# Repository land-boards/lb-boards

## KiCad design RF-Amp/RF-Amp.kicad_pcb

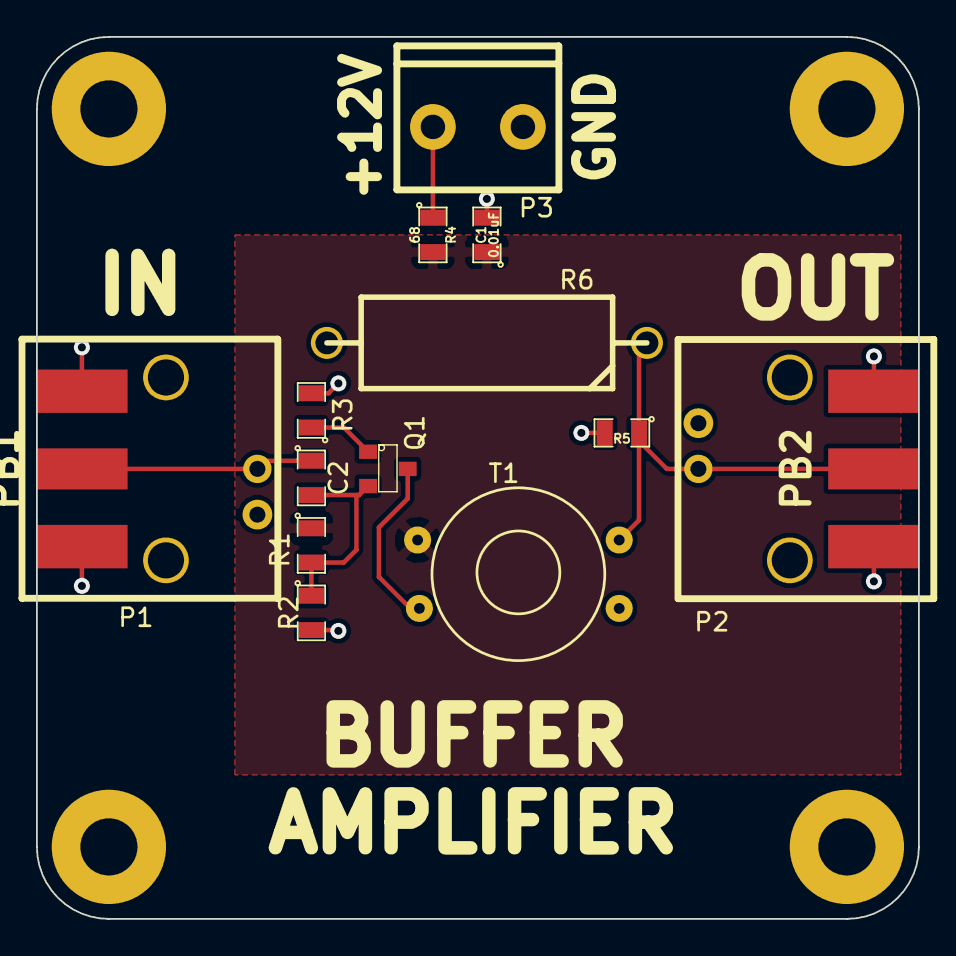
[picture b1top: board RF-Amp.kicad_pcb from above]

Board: 2 copper layers, 49.0 x 49.0 mm, 19 parts (0 on the bottom side), 8 nets.

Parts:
C1: 0.01uF; SM0805
C2: C; SM0805
MTG1, MTG2, MTG3, MTG4: CONN_1; MTG-4-40
P1, P2: BNC; BNC-RT
P3: CONN_2; TB2-5MM
PB1, PB2: CONN_2; SMA_EDGE
Q1: 2N3904; SOT23
R1: 22K; SM0805
R2: R; SM0805
R3: 180; SM0805
R4: 68; SM0805
R5: DNP; SM0805
R6: DNP; R7
T1: TRANSFO; TRANS-37-43

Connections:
/+12V: P3.1, R4.1
/+BUF: C1.1, R1.1, R4.2, T1.1
/GND: C1.2, P1.2, P2.2, P3.2, PB1.2, PB2.2, R2.2, R3.2, R5.2, R6.2, T1.3
/IN: C2.1, P1.1, PB1.1
/OUT: P2.1, PB2.1, R5.1, R6.1, T1.4
/VB: C2.2, Q1.2, R1.2, R2.1
/VC: Q1.3, T1.2
unnamed: Q1.1, R3.1

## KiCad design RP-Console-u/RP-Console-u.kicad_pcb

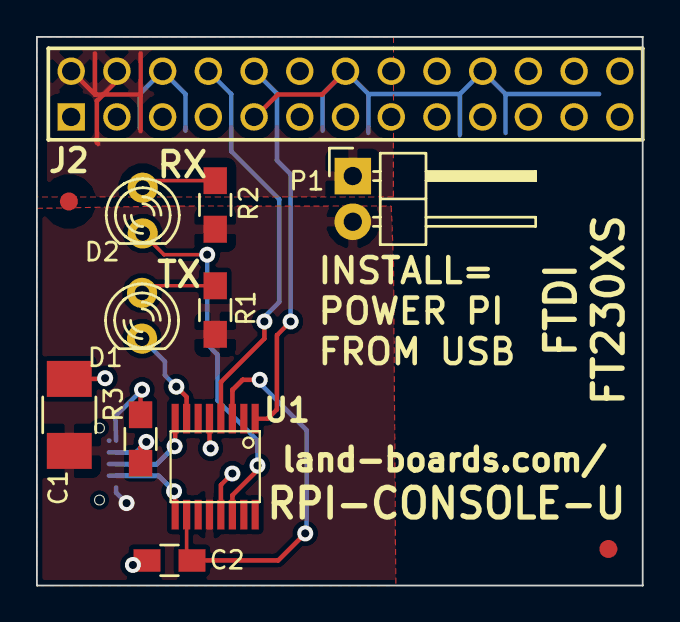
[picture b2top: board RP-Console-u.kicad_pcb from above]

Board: 2 copper layers, 33.7 x 30.5 mm, 13 parts (1 on the bottom side), 13 nets.

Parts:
C1: 10uF; C_1210_HandSoldering
C2: 0.1uF; C_0805_HandSoldering
D1, D2: LED; LED-3MM
FID1, FID2: CONN_1; FIDUCIAL
J1: USB-MICRO-B; USB_Micro-B-Wellco-SMT
J2: RASPIO; pin_array_13x2
P1: CONN_2; Pin_Header_Angled_1x02
R1, R2: 270; R_0805_HandSoldering
R3: 130K; R_0805_HandSoldering
U1: FT230XS; ssop-16

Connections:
/+3.3V-USB: C2.1, U1.3, U1.10
/+5V: J2.2, J2.4, P1.1
/+5V-USB: C1.1, J1.1, P1.2, R1.1, R2.1, U1.12
/DM: J1.2, U1.9
/DP: J1.3, U1.8
/GND: C1.2, C2.2, J1.5, J2.6, J2.9, J2.14, J2.20, J2.25, R3.2, U1.5, U1.13
/PI2USB: J2.8, U1.4
/PUP0: D1.1, R1.2
/PUP1: D2.1, R2.2
/RXLED*: D2.2, U1.14
/TXLED*: D1.2, U1.7
/USB2PI: J2.10, U1.1
unnamed: J1.4, R3.1

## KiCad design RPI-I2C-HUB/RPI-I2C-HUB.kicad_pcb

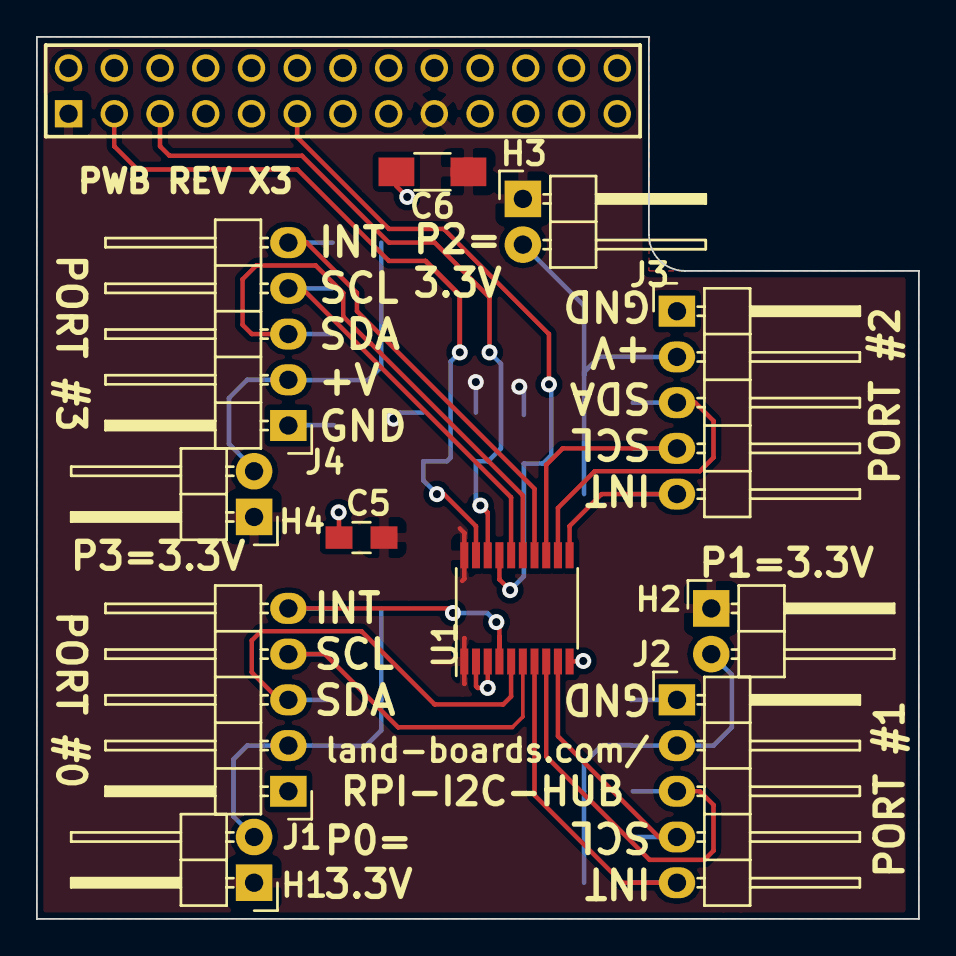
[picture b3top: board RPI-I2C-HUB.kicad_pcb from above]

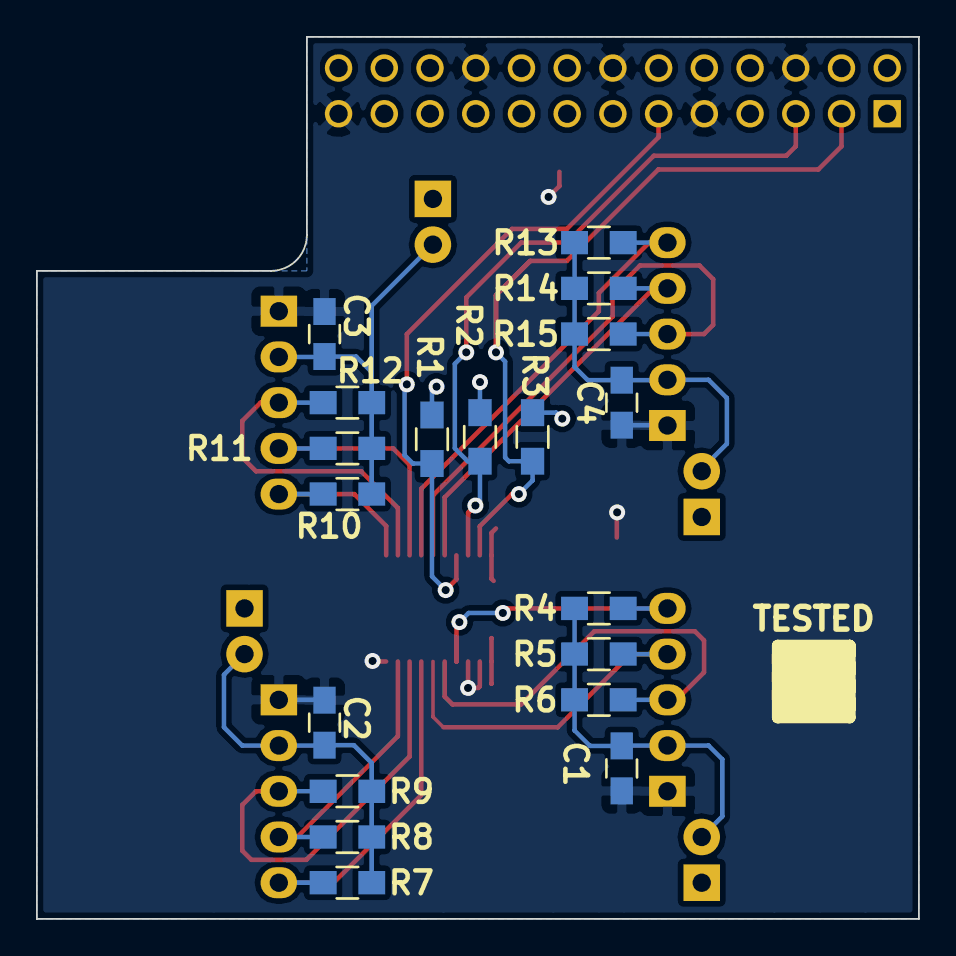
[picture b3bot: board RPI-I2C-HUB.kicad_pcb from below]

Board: 2 copper layers, 49.0 x 49.0 mm, 32 parts (19 on the bottom side), 21 nets.

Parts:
C1, C2, C3, C4, C5: 0.1uF; C_0805_HandSoldering
C6: 10uF; C_1206_HandSoldering
H1, H2, H3, H4: CONN_01X02; Pin_Header_Angled_1x02
J1, J2, J3, J4: I2CINT-5PIN; Pin_Header_Angled_1x05
P1: RASPIO; pin_array_13x2
R1, R2, R3, R4, R5, R6, R7, R8, R9, R10, R11, R12, R13, R14, R15: 3.3K; R_0805_HandSoldering
TESTED: VAL**; TEST_BLK-REAR
U1: PCA9544A; TSSOP-20_4.4x6.5mm_Pitch0.65mm

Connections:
+3.3V: C5.1, C6.1, H1.1, H2.1, H3.1, H4.1, P1.1, P1.17, R1.1, R2.1, R3.1, U1.1, U1.20
/IO_17: P1.11, R1.2, U1.17
/SCLK1: P1.5, R2.2, U1.18
/SDA1: P1.3, R3.2, U1.19
/~I0: J1.5, R4.2, U1.4
/~I1: J2.5, R7.2, U1.7
/~I2: J3.5, R10.2, U1.11
/~I3: J4.5, R13.2, U1.14
GND: C1.2, C2.2, C3.2, C4.2, C5.2, C6.2, J1.1, J2.1, J3.1, J4.1, P1.6, P1.9, P1.14, P1.20, P1.25, U1.2, U1.3, U1.10
unnamed: C1.1, H1.2, J1.2, R4.1, R5.1, R6.1
unnamed: C2.1, H2.2, J2.2, R7.1, R8.1, R9.1
unnamed: C3.1, H3.2, J3.2, R10.1, R11.1, R12.1
unnamed: C4.1, H4.2, J4.2, R13.1, R14.1, R15.1
unnamed: J1.3, R6.2, U1.5
unnamed: J1.4, R5.2, U1.6
unnamed: J2.3, R9.2, U1.8
unnamed: J2.4, R8.2, U1.9
unnamed: J3.3, R12.2, U1.12
unnamed: J3.4, R11.2, U1.13
unnamed: J4.3, R15.2, U1.15
unnamed: J4.4, R14.2, U1.16
